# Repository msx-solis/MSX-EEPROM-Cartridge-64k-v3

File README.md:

# MSX EEPROM Cartridge 64K v3

Front side

Back side

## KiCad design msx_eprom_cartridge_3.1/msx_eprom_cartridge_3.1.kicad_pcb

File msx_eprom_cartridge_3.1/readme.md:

# MSX EEPROM Cartridge 64k v3
This PCB is a board to be used as ROM software loader. Is compatible with many ROM chips and all non banked software up to 64Kb.

Front view

Back view

More info at:

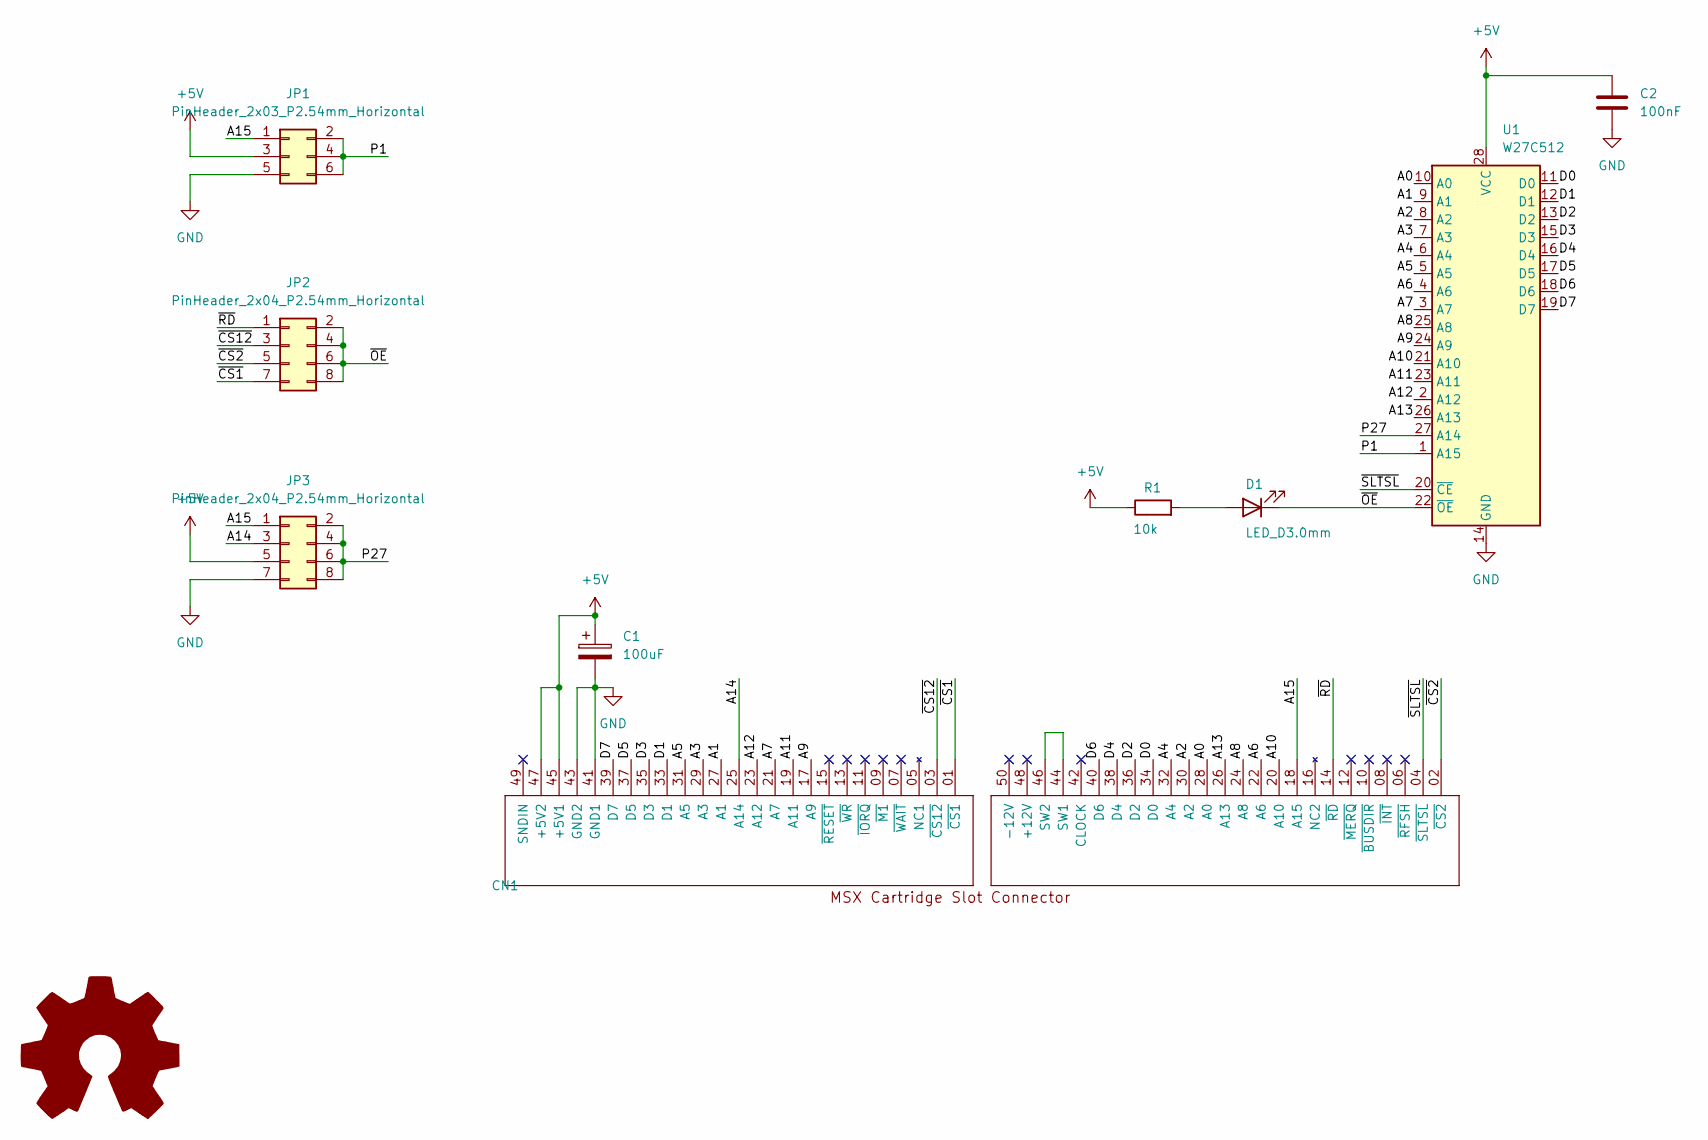
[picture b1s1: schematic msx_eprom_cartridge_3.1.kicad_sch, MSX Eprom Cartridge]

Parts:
C1: 100uF; CP_tumbado
C2: 100nF; C_Disc_D4.3mm_W1.9mm_P5.00mm
CN1: MSX_SLOT_CON; CARTRIDGE_#_MSX_XL
D1: LED_D3.0mm; LED_D3.0mm_Horizontal_O1.27mm_Z2.0mm
JP1: PinHeader_2x03_P2.54mm_Horizontal
JP2, JP3: PinHeader_2x04_P2.54mm_Horizontal
LO1: LOGO; Logo_MSXmakers_fsilk_29x14_neg
R1: 10k; R_Axial_DIN0207_L6.3mm_D2.5mm_P10.16mm_Horizontal
U1: W27C512; DIP-28c_W15.24mm_Socket_LongPads

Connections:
+5V: C1.1, C2.1, CN1.45 (+5V1), CN1.47 (+5V2), JP1.3, JP3.5, R1.1, U1.28 (VCC)
/A0: CN1.28 (A0), U1.10 (A0)
/A1: CN1.27 (A1), U1.9 (A1)
/A2: CN1.30 (A2), U1.8 (A2)
/A3: CN1.29 (A3), U1.7 (A3)
/A4: CN1.32 (A4), U1.6 (A4)
/A5: CN1.31 (A5), U1.5 (A5)
/A6: CN1.22 (A6), U1.4 (A6)
/A7: CN1.21 (A7), U1.3 (A7)
/A8: CN1.24 (A8), U1.25 (A8)
/A9: CN1.17 (A9), U1.24 (A9)
/A10: CN1.20 (A10), U1.21 (A10)
/A11: CN1.19 (A11), U1.23 (A11)
/A12: CN1.23 (A12), U1.2 (A12)
/A13: CN1.26 (A13), U1.26 (A13)
/A14: CN1.25 (A14), JP3.3
/A15: CN1.18 (A15), JP1.1, JP3.1
/D0: CN1.34 (D0), U1.11 (D0)
/D1: CN1.33 (D1), U1.12 (D1)
/D2: CN1.36 (D2), U1.13 (D2)
/D3: CN1.35 (D3), U1.15 (D3)
/D4: CN1.38 (D4), U1.16 (D4)
/D5: CN1.37 (D5), U1.17 (D5)
/D6: CN1.40 (D6), U1.18 (D6)
/D7: CN1.39 (D7), U1.19 (D7)
/P1: JP1.2, JP1.4, JP1.6, U1.1 (A15)
/P27: JP3.2, JP3.4, JP3.6, JP3.8, U1.27 (A14)
/~CS1: CN1.01 (~CS1), JP2.7
/~CS2: CN1.02 (~CS2), JP2.5
/~CS12: CN1.03 (~CS12), JP2.3
/~OE: D1.1 (K), JP2.2, JP2.4, JP2.6, JP2.8, U1.22 (~OE)
/~RD: CN1.14 (~RD), JP2.1
/~SLTSL: CN1.04 (~SLTSL), U1.20 (~CE)
GND: C1.2, C2.2, CN1.41 (GND1), CN1.43 (GND2), JP1.5, JP3.7, U1.14 (GND)
unnamed: CN1.44 (SW1), CN1.46 (SW2)
unnamed: D1.2 (A), R1.2

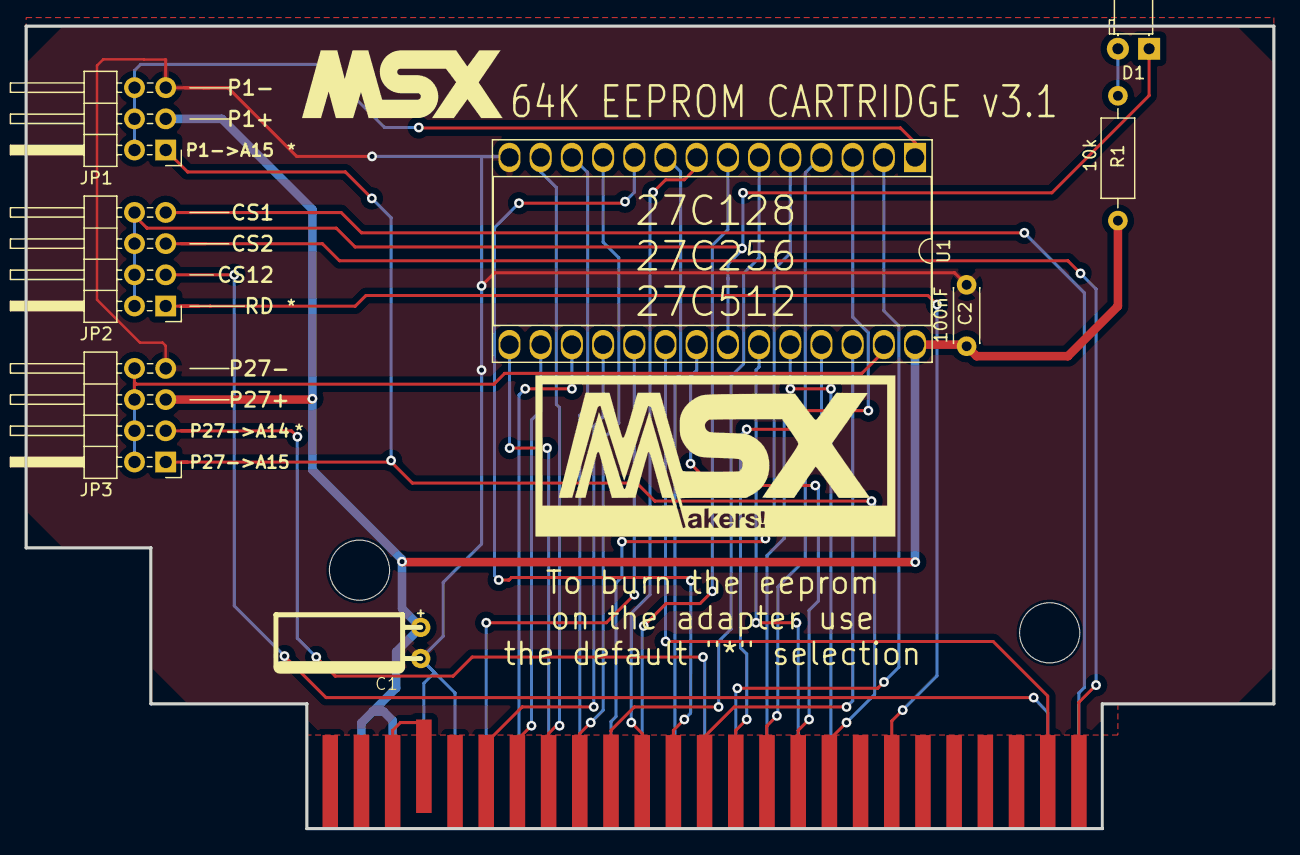
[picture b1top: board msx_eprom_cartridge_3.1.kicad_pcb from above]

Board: 2 copper layers, 101.6 x 65.3 mm, 10 parts (0 on the bottom side), 36 nets.
